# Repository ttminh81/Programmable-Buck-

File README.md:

# Programmable-Buck-
Programmable Buck used for testing and power supply

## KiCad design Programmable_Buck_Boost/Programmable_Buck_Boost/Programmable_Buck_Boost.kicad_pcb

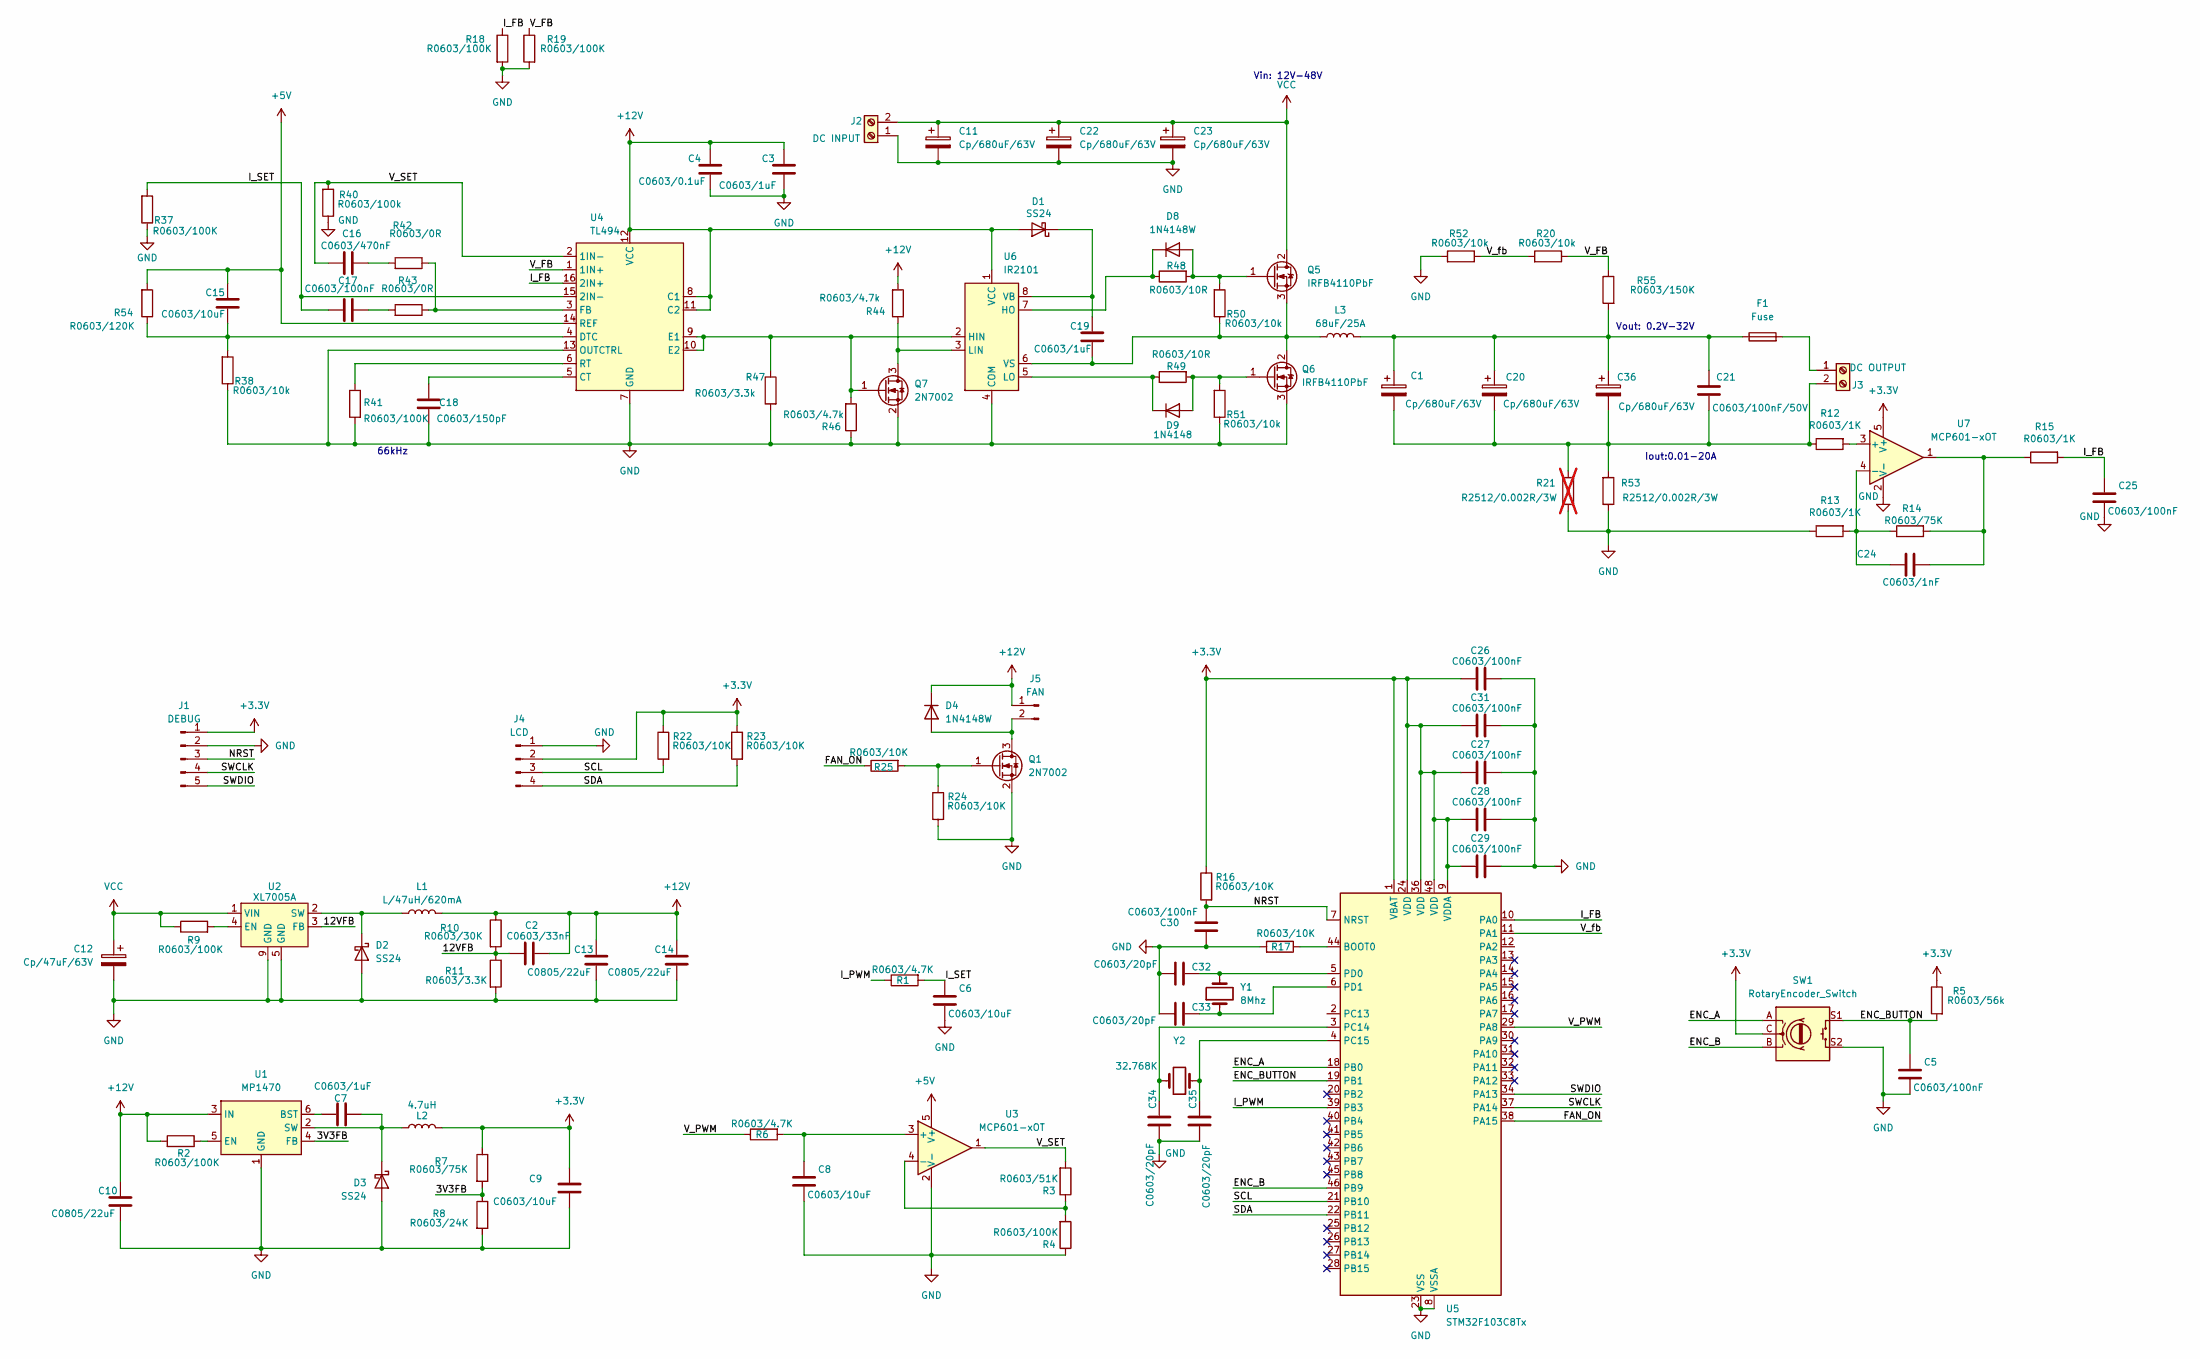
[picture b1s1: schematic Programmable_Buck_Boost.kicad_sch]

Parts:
C1, C11, C20, C22, C23, C36: Cp/680uF/63V; CP_Radial_D13.0mm_P5.00mm
C2: C0603/33nF; C_0603_1608Metric
C3, C7, C19: C0603/1uF; C_0603_1608Metric
C4: C0603/0.1uF; C_0603_1608Metric
C5, C17, C25, C26, C27, C28, C29, C30, C31: C0603/100nF; C_0603_1608Metric
C6, C8, C9, C15: C0603/10uF; C_0603_1608Metric
C10, C13, C14: C0805/22uF; C_0805_2012Metric
C12: Cp/47uF/63V; CP_Radial_D8.0mm_P3.50mm
C16: C0603/470nF; C_0603_1608Metric
C18: C0603/150pF; C_0603_1608Metric
C21: C0603/100nF/50V; C_0603_1608Metric
C24: C0603/1nF; C_0603_1608Metric
C32, C33, C34, C35: C0603/20pF; C_0603_1608Metric
D1, D2, D3: SS24; D_SMA
D4, D8: 1N4148W; D_SOD-123
D9: 1N4148; D_SOD-123
F1: Fuse; Fuse_Blade_Mini_directSolder
J1: DEBUG; JST_XH_B5B-XH-AM_1x05_P2.50mm_Vertical
J2: DC INPUT; TerminalBlock_Dinkle_DT-55-B01X-02_P10.00mm
J3: DC OUTPUT; TerminalBlock_Dinkle_DT-55-B01X-02_P10.00mm
J4: LCD; PinSocket_1x04_P2.54mm_Vertical
J5: FAN; JST_XH_B2B-XH-A_1x02_P2.50mm_Vertical
L1: L/47uH/620mA; L_Abracon_ASPI-0425
L2: 4.7uH; L_APV_APH0412
L3: 68uF/25A; Inductor_36x23x15MM
Q1, Q7: 2N7002; SOT-23
Q5, Q6: IRFB4110PbF; TO-220-3_Vertical
R1, R6: R0603/4.7K; R_0603_1608Metric
R2, R4, R9, R18, R19, R37, R41: R0603/100K; R_0603_1608Metric
R3: R0603/51K; R_0603_1608Metric
R5: R0603/56k; R_0603_1608Metric
R7, R14: R0603/75K; R_0603_1608Metric
R8: R0603/24K; R_0603_1608Metric
R10: R0603/30K; R_0603_1608Metric
R11: R0603/3.3K; R_0603_1608Metric
R12, R13, R15: R0603/1K; R_0603_1608Metric
R16, R17, R22, R23, R24, R25: R0603/10K; R_0603_1608Metric
R20, R38, R50, R51, R52: R0603/10k; R_0603_1608Metric
R21: R2512/0.002R/3W; R_2512_6332Metric; not fitted
R40: R0603/100k; R_0603_1608Metric
R42, R43: R0603/0R; R_0603_1608Metric
R44, R46: R0603/4.7k; R_0603_1608Metric
R47: R0603/3.3k; R_0603_1608Metric
R48, R49: R0603/10R; R_0603_1608Metric
R53: R2512/0.002R/3W; R_2512_6332Metric
R54: R0603/120K; R_0603_1608Metric
R55: R0603/150K; R_0603_1608Metric
SW1: RotaryEncoder_Switch; RotaryEncoder_Alps_EC11E-Switch_Vertical_H20mm
U1: MP1470; TSOT-23-6
U2: XL7005A; SOIC-8-1EP_3.9x4.9mm_P1.27mm_EP2.29x3mm
U3, U7: MCP601-xOT; SOT-23-5
U4: TL494; SOP-16_4.4x10.4mm_P1.27mm
U5: STM32F103C8Tx; LQFP-48_7x7mm_P0.5mm
U6: IR2101; SOIC-8_3.9x4.9mm_P1.27mm
Y1: 8Mhz; Crystal_SMD_5032-2Pin_5.0x3.2mm
Y2: 32.768K; Crystal_SMD_3215-2Pin_3.2x1.5mm

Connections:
+3.3V: C9.1, C26.1, C27.1, C28.1, C29.1, C31.1, J1.1, J4.2, L2.2, R5.1, R7.1, R16.1, R22.1, R23.1, SW1.C, U5.1 (VBAT), U5.9 (VDDA), U5.24 (VDD), U5.36 (VDD), U5.48 (VDD), U7.5 (V+)
+5V: C15.1, R54.2, U3.5 (V+), U4.14 (REF)
+12V: C2.2, C3.1, C4.1, C10.1, C13.1, C14.1, D1.2 (A), D4.1 (K), J5.1, L1.2, R2.2, R10.1, R44.2, U1.3 (IN), U4.8 (C1), U4.11 (C2), U4.12 (VCC), U6.1 (VCC)
/3V3FB: R7.2, R8.1, U1.4 (FB)
/12VFB: C2.1, R10.2, R11.1, U2.3 (FB)
/ENC_A: SW1.A, U5.18 (PB0)
/ENC_B: SW1.B, U5.46 (PB9)
/ENC_BUTTON: C5.1, R5.2, SW1.S1, U5.19 (PB1)
/FAN_ON: R25.1, U5.38 (PA15)
/I_FB: C25.1, R15.2, R18.1, U4.16 (2IN+), U5.10 (PA0)
/I_PWM: R1.1, U5.39 (PB3)
/I_SET: C6.1, C17.2, R1.2, R37.2, U4.15 (2IN-)
/NRST: C30.2, J1.3, R16.2, U5.7 (NRST)
/SCL: J4.3, R22.2, U5.21 (PB10)
/SDA: J4.4, R23.2, U5.22 (PB11)
/SWCLK: J1.4, U5.37 (PA14)
/SWDIO: J1.5, U5.34 (PA13)
/V_FB: R19.1, R20.1, R55.1, U4.1 (1IN+)
/V_PWM: R6.1, U5.29 (PA8)
/V_SET: C16.2, R3.2, R40.2, U3.1, U4.2 (1IN-)
/V_fb: R20.2, R52.1, U5.11 (PA1)
GND: C3.2, C4.2, C5.2, C6.2, C8.2, C9.2, C10.2, C11.2, C12.2, C13.2, C14.2, C18.1, C22.2, C23.2, C25.2, C26.2, C27.2, C28.2, C29.2, C30.1, C31.2, C32.2, C33.2, C34.2, C35.2, D2.2 (A), D3.2 (A), J1.2, J2.1, J4.1, Q1.2 (S), Q6.3 (S), Q7.2 (S), R4.1, R8.2, R11.2, R13.1, R17.2, R18.2, R19.2, R21.1, R24.2, R37.1, R38.1, R40.1, R41.2, R46.1, R47.2, R51.1, R52.2, R53.1, SW1.S2, U1.1 (GND), U2.5 (GND), U2.6 (GND), U2.7 (GND), U2.8 (GND), U2.9 (GND), U3.2 (V-), U4.7 (GND), U4.13 (OUTCTRL), U5.8 (VSSA), U5.23 (VSS), U5.35 (VSS), U5.47 (VSS), U6.4 (COM), U7.2 (V-)
unnamed: C1.1, C20.1, C21.1, C36.1, F1.1, L3.2, R55.2
unnamed: C16.1, R42.2
unnamed: C17.1, R43.2
unnamed: C24.1, R14.2, R15.1, U7.1
unnamed: C19.1, D1.1 (K), U6.8 (VB)
unnamed: D2.1 (K), L1.1, U2.2 (SW)
unnamed: C7.1, D3.1 (K), L2.1, U1.2 (SW)
unnamed: D4.2 (A), J5.2, Q1.3 (D)
unnamed: D8.2 (A), Q5.1 (G), R48.2, R50.2
unnamed: D8.1 (K), R48.1, U6.7 (HO)
unnamed: D9.2 (A), Q6.1 (G), R49.2, R51.2
unnamed: D9.1 (K), R49.1, U6.5 (LO)
unnamed: F1.2, J3.1
unnamed: C1.2, C20.2, C21.2, C36.2, J3.2, R12.1, R21.2, R53.2
unnamed: Q1.1 (G), R24.1, R25.2
unnamed: C19.2, L3.1, Q5.3 (S), Q6.2 (D), R50.1, U6.6 (VS)
unnamed: Q7.3 (D), R44.1, U6.3 (LIN)
unnamed: Q7.1 (G), R46.2, R47.1, U4.9 (E1), U4.10 (E2), U6.2 (HIN)
unnamed: C7.2, U1.6 (BST)
unnamed: R2.1, U1.5 (EN)
unnamed: R9.2, U2.4 (EN)
unnamed: C8.1, R6.2, U3.3 (+)
unnamed: R3.1, R4.2, U3.4 (-)
unnamed: C18.2, U4.5 (CT)
unnamed: C15.2, R38.2, R54.1, U4.4 (DTC)
unnamed: R42.1, R43.1, U4.3 (FB)
unnamed: R41.1, U4.6 (RT)
unnamed: R17.1, U5.44 (BOOT0)
unnamed: C34.1, U5.3 (PC14), Y2.2
unnamed: C35.1, U5.4 (PC15), Y2.1
unnamed: C32.1, U5.5 (PD0), Y1.2
unnamed: C33.1, U5.6 (PD1), Y1.1
unnamed: R12.2, U7.3 (+)
unnamed: C24.2, R13.2, R14.1, U7.4 (-)
VCC: C11.1, C12.1, C22.1, C23.1, J2.2, Q5.2 (D), R9.1, U2.1 (VIN)

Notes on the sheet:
Vout: 0.2V-32V
66kHz
Vin: 12V-48V
Iout:0.01-20A

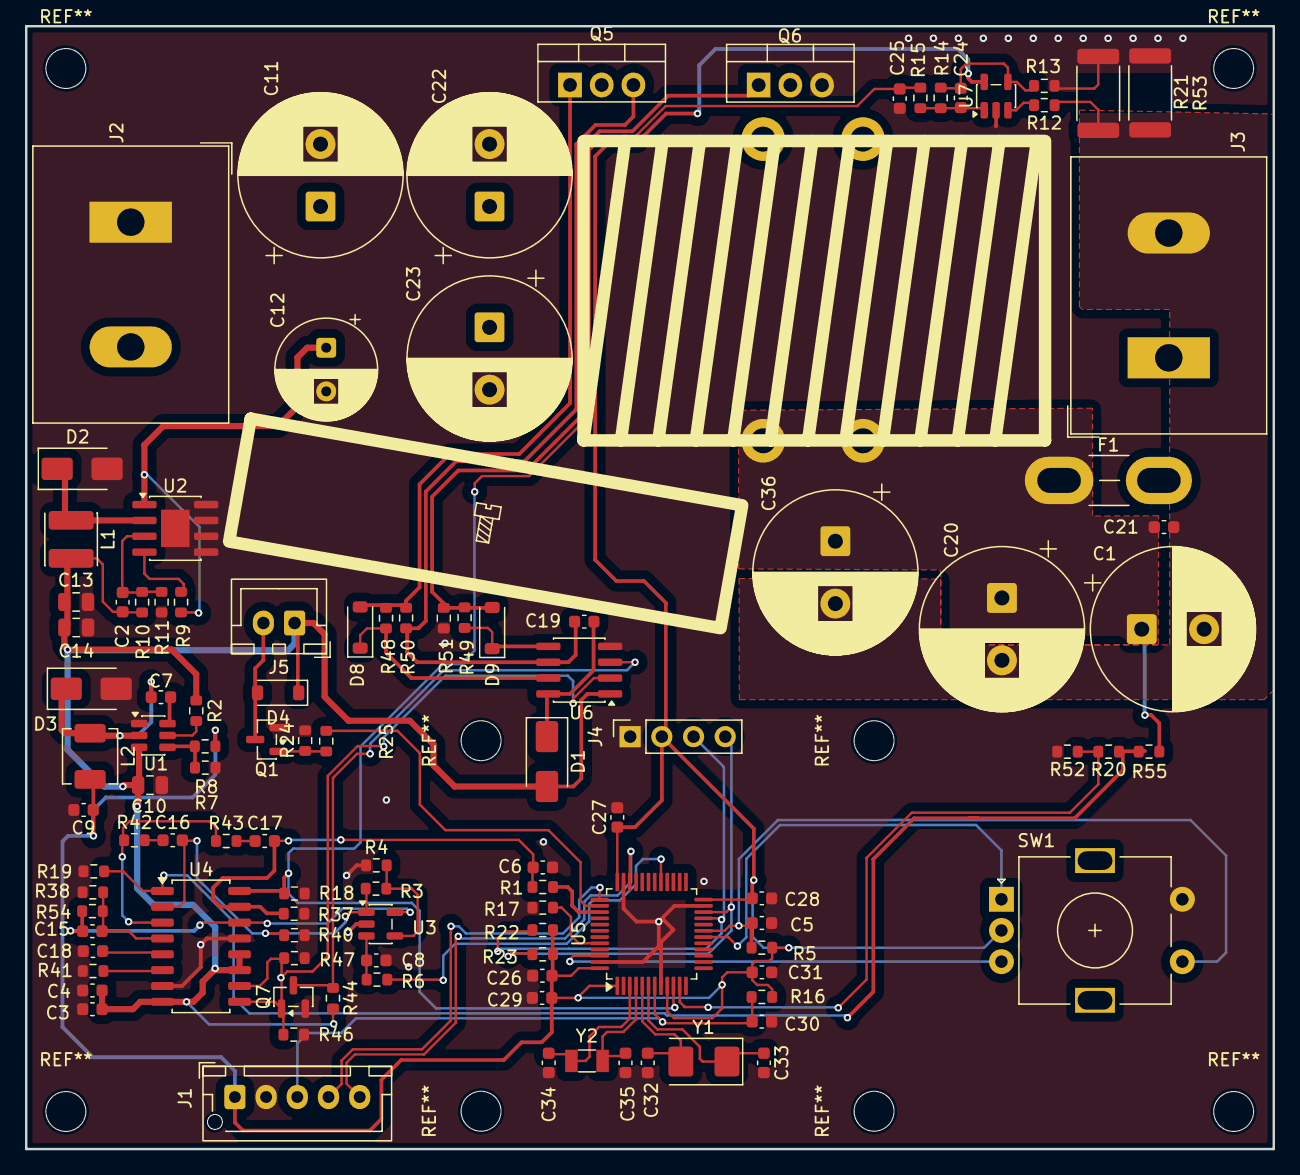
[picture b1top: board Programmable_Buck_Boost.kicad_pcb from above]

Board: 2 copper layers, 100.0 x 90.0 mm, 107 parts (0 on the bottom side), 57 nets.

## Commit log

2025-10-07 Add schematic file
2025-12-31 Finalize Schematic
2026-01-06 Add current sense circuit
2026-01-08 Change design
2026-01-09 Place component on board
2026-01-11 Finalize PCb
